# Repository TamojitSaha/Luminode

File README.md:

<h1 align="center"> LumiNode </h1> <br>

## Table of Contents
- [Introduction](#introduction)
- [Bill of Materials](#bill-of-materials)
- [Features](#features)
- [Contributors](#Contributors)
- [License](#license)
- [Acknowledgments](#acknowledgments)

## Introduction

A wireless multipurpose IoT (Internet of Things) compatible smart light system that can reproduce colour from any image in RGB colour space with intensity adjustment capability.
It is open-source and built for Arduino ecosystem making it suitable for hobbysist and beginners.
<p align="center">
  &nbsp 
  &nbsp 
</p>
<p align="center">
  &nbsp
  &nbsp
</p>
<p align="center">
  &nbsp
</p>

## Bill of Materials

        1. Arduino Pro Mini
        2. 7805 Voltage regulator
        3. Bluetooth module HC-05
        4. 4 x 3528 RGB LEDs
        5. 4 x 100 to 330ohm resistors in 0805 package
        6. 1 x ULN2003 smd
        7. 1 x MMBT2N2222
        8. 1 x 1Kohm in 0805 package
        9. 4 x 330ohm in 1206 package
        10. 1 x M7 diode(1N4007 smd version) 
        11. 1W cool white smd LED
        12. PCB fabrication materials.
        13. Single core wires for soldering PTH holes.
        14. DBS107G - Bridge Rectifier
        15. 2 x 10K in 1206 package
        16. 2 x 100nF in 0805 package
        17. 1 x ferrite chip 0805 package(optional: pads can be shorted in PCB)
        18. 1 x 1A PTC 0805 package(optional: pads can be shorted in PCB

## Features
- Simple UI
- Colour selection from any chosen image
- Real-time colour synchronization

## Contributors
Connect us here:
<br><br>
 <br>
 
<p> 
or <a href ="https://github.com/SandeepanSengupta/Luminode/issues/new/">file an issue</a>. Feature requests are always welcome.</p>

## License
Contents of this repository are realeased under [CC-BY-NC-SA 4.0](./LICENSE.md) <br>

## Acknowledgments
Thanks to the contributors! :wink:

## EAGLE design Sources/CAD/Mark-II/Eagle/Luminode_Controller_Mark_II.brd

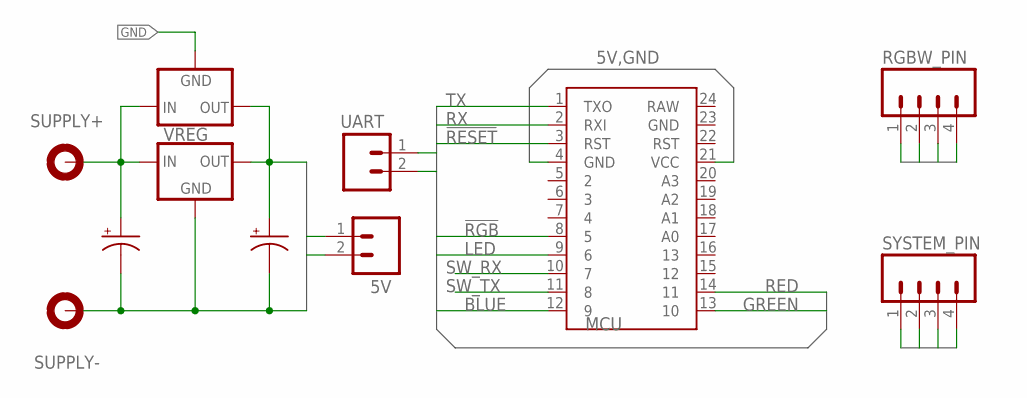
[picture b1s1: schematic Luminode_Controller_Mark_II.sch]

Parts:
5V: M02PTH; 1X02
C_IN: CPOL-USSMCB; SMC_B
C_OUT: CPOL-USSMCB; SMC_B
MCU: ARDUINO_MINI
RGBW_PIN: M04PTH; 1X04
SUPPLY+: +V; 3,0-PAD
SUPPLY-: -V; 3,0-PAD
SYSTEM_PIN: M04PTH; 1X04
UART: M02PTH; 1X02
VREG: 7805; SOT223
VREG_ALT: V_REG_78XXSINK; TO220-IGO

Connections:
5V: 5V.1, C_OUT.+, MCU.21 (VCC), SYSTEM_PIN.1, VREG.2 (OUT), VREG_ALT.OUT
!RESET: MCU.3 (RST)
!RGB: MCU.8 (5), SYSTEM_PIN.4
BLUE: MCU.12 (9), RGBW_PIN.3
GND: 5V.2, C_IN.-, C_OUT.-, MCU.4 (GND), SUPPLY-.B3,0, SYSTEM_PIN.3, VREG.1 (GND), VREG_ALT.GND
GREEN: MCU.13 (10), RGBW_PIN.2
LED: MCU.9 (6), RGBW_PIN.4
RED: MCU.14 (11), RGBW_PIN.1
RX: MCU.2 (RXI)
SW_RX: MCU.10 (7), UART.2
SW_TX: MCU.11 (8), UART.1
TX: MCU.1 (TXO)
VIN: C_IN.+, SUPPLY+.B3,0, SYSTEM_PIN.2, VREG.3 (IN), VREG_ALT.IN

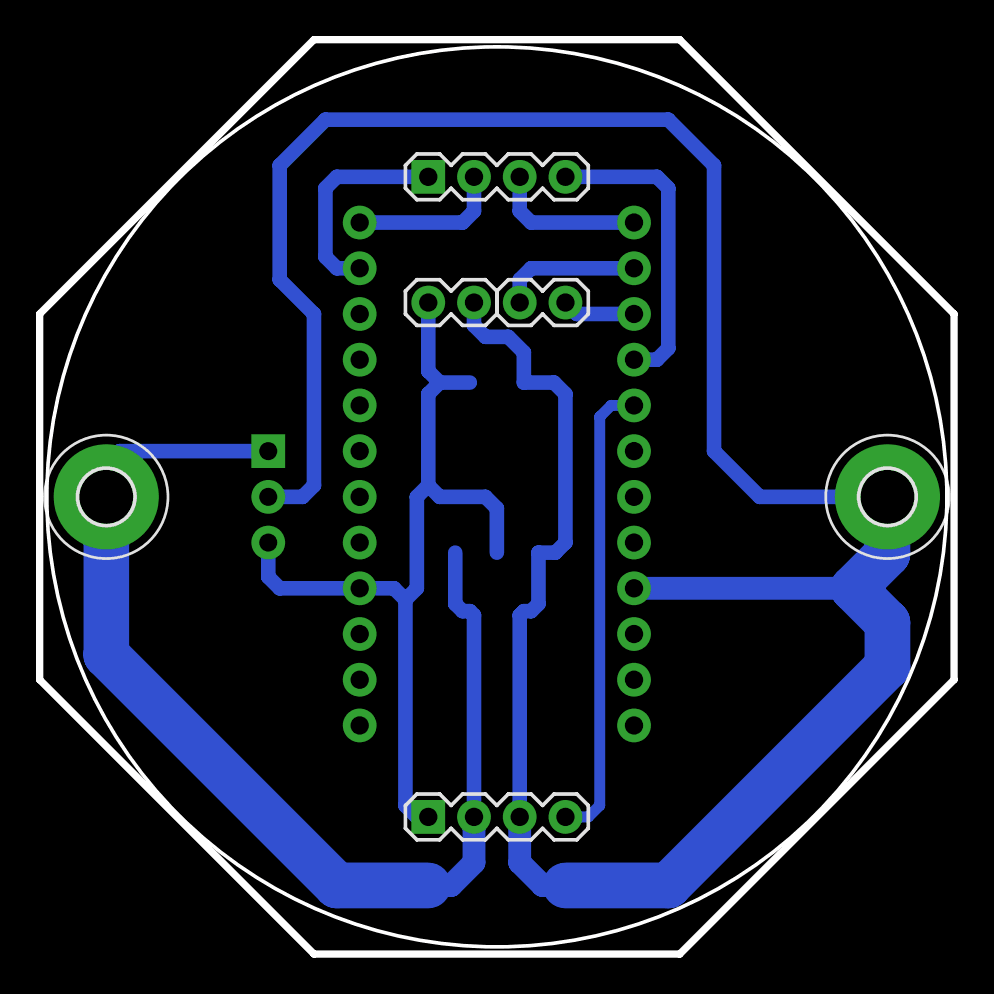
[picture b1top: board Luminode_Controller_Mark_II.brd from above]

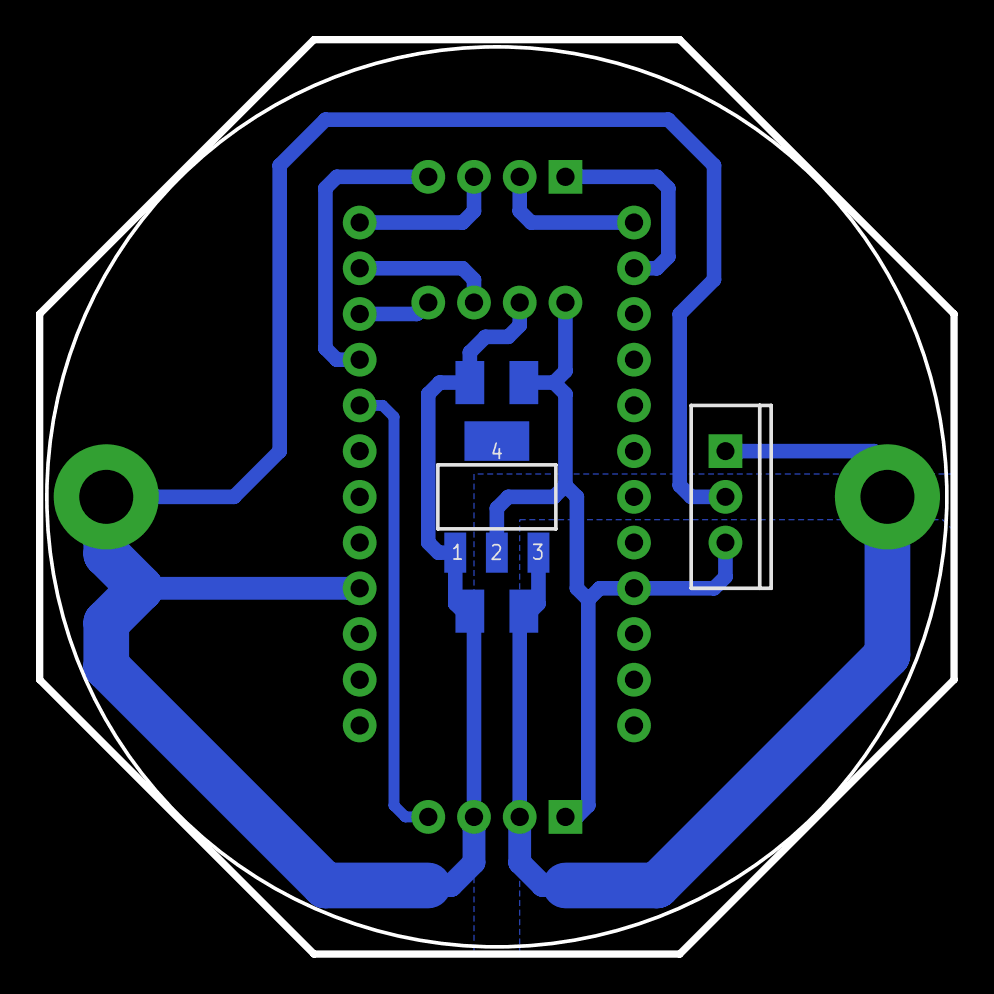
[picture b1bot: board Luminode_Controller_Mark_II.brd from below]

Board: 2 copper layers, 50.8 x 50.8 mm, 11 parts (4 on the bottom side), 10 nets.

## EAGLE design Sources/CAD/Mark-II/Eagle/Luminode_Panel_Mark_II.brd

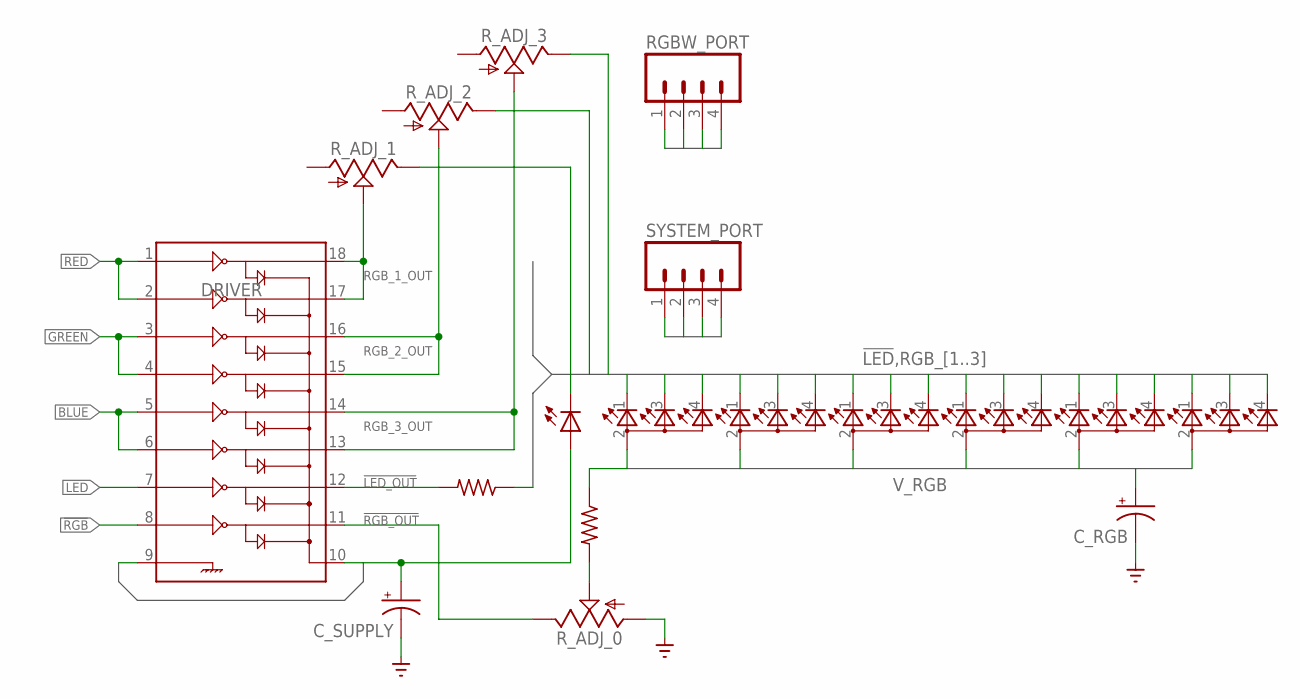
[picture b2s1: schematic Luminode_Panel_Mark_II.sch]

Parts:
C_RGB: CPOL-USE2.5-6; E2,5-6
C_SUPPLY: CPOL-USE2.5-6; E2,5-6
DRIVER: ULN2803SOICW; SO18L
LED: X42180; Z-POWER-LED-DOME-TYPE
LED_RGB_1, LED_RGB_2, LED_RGB_3, LED_RGB_4, LED_RGB_5, LED_RGB_6: TOPLED-3PLCC; P-LCC-4-3
RGBW_PORT: M04PTH; 1X04
R_ADJ_0, R_ADJ_1, R_ADJ_2, R_ADJ_3: 500E; B25P
R_LED: R-US_0309/10; 0309/10
R_RGB: R-US_0207/7; 0207/7
SYSTEM_PORT: M04PTH; 1X04

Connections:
5V: SYSTEM_PORT.1
!LED: LED.C, R_LED.1
!LED_OUT: DRIVER.12, R_LED.2
!RGB: DRIVER.8, SYSTEM_PORT.4
!RGB_OUT: DRIVER.11, R_ADJ_0.E
BLUE: DRIVER.5, DRIVER.6, RGBW_PORT.3
GND: C_RGB.-, C_SUPPLY.-, DRIVER.9, R_ADJ_0.A, SYSTEM_PORT.3
GREEN: DRIVER.3, DRIVER.4, RGBW_PORT.2
LED: DRIVER.7, RGBW_PORT.4
unnamed: R_ADJ_0.S, R_RGB.2
RED: DRIVER.1, DRIVER.2, RGBW_PORT.1
RGB_1: LED_RGB_1.1 (CRED), LED_RGB_2.1 (CRED), LED_RGB_3.1 (CRED), LED_RGB_4.1 (CRED), LED_RGB_5.1 (CRED), LED_RGB_6.1 (CRED), R_ADJ_1.E
RGB_1_OUT: DRIVER.17, DRIVER.18, R_ADJ_1.S
RGB_2: LED_RGB_1.3 (CBLUE), LED_RGB_2.3 (CBLUE), LED_RGB_3.3 (CBLUE), LED_RGB_4.3 (CBLUE), LED_RGB_5.3 (CBLUE), LED_RGB_6.3 (CBLUE), R_ADJ_2.E
RGB_2_OUT: DRIVER.15, DRIVER.16, R_ADJ_2.S
RGB_3: LED_RGB_1.4 (CGREEN), LED_RGB_2.4 (CGREEN), LED_RGB_3.4 (CGREEN), LED_RGB_4.4 (CGREEN), LED_RGB_5.4 (CGREEN), LED_RGB_6.4 (CGREEN), R_ADJ_3.E
RGB_3_OUT: DRIVER.13, DRIVER.14, R_ADJ_3.S
VIN: C_SUPPLY.+, DRIVER.10, LED.A, SYSTEM_PORT.2
V_RGB: C_RGB.+, LED_RGB_1.2 (A2), LED_RGB_2.2 (A2), LED_RGB_3.2 (A2), LED_RGB_4.2 (A2), LED_RGB_5.2 (A2), LED_RGB_6.2 (A2), R_RGB.1

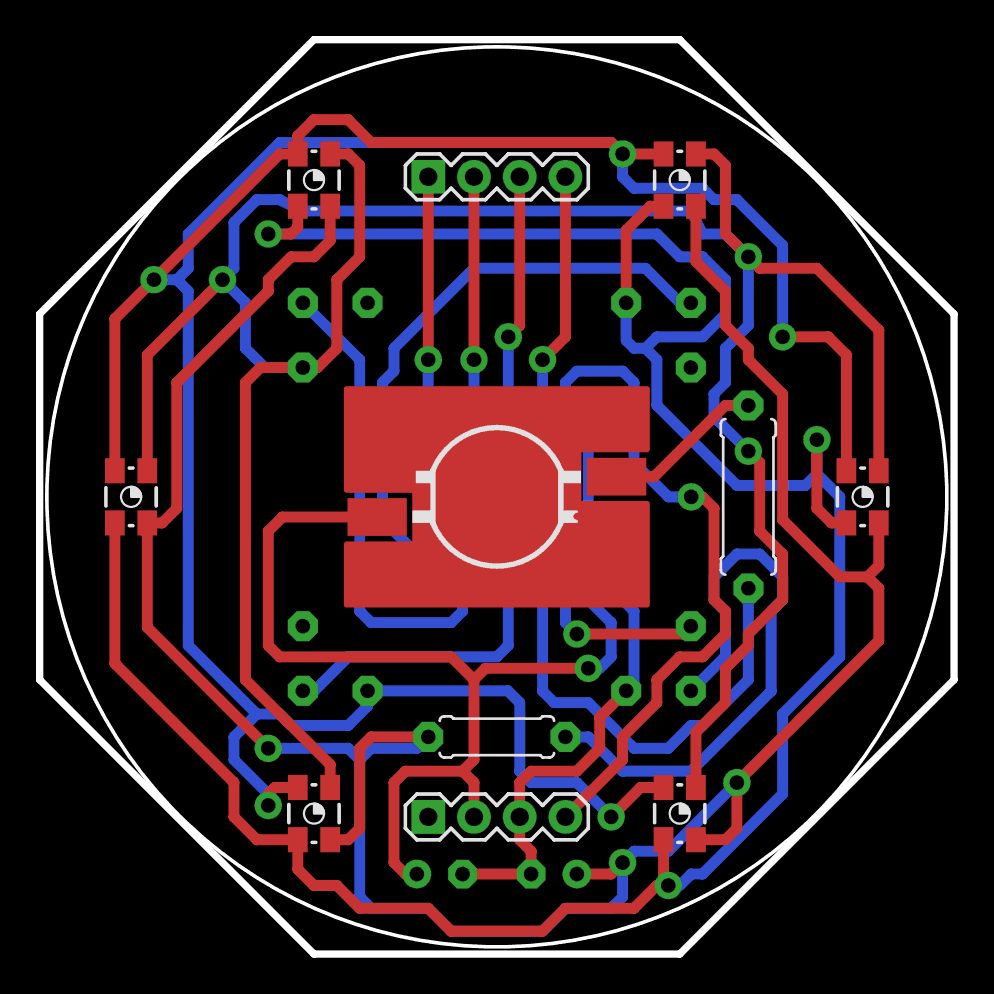
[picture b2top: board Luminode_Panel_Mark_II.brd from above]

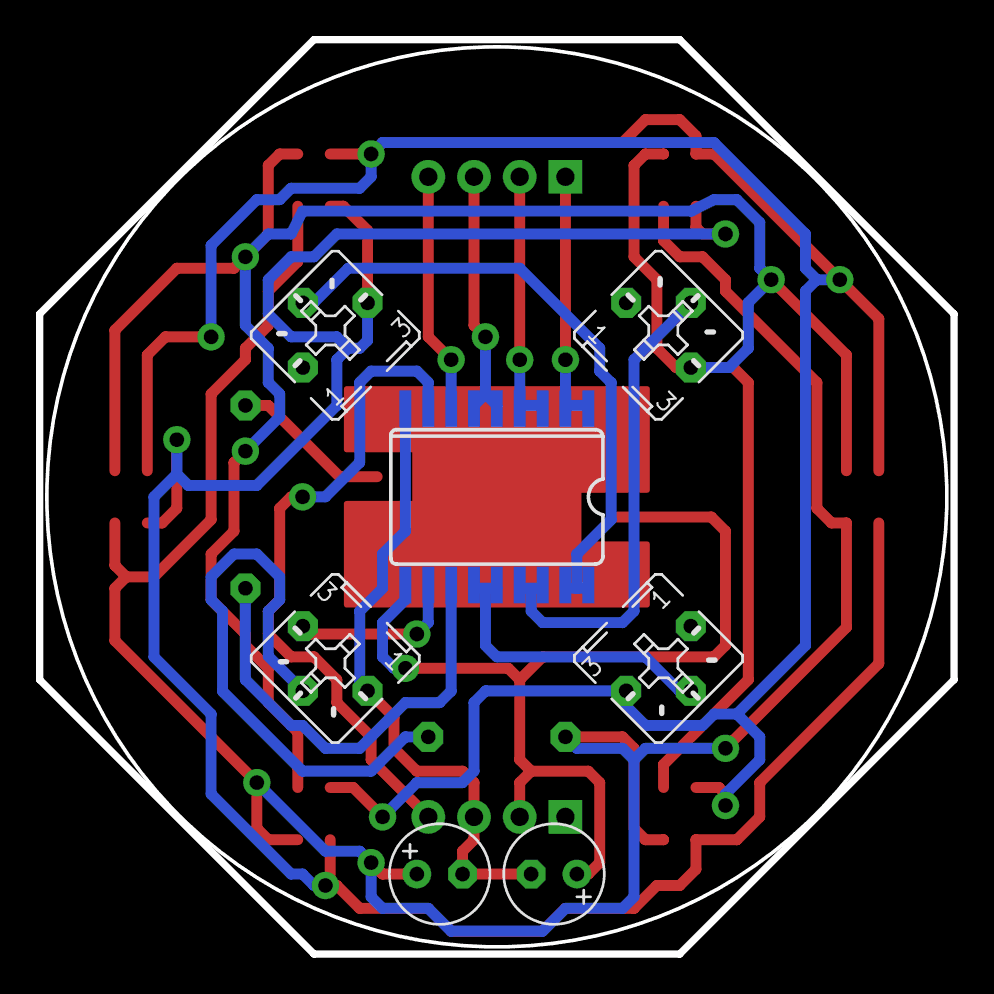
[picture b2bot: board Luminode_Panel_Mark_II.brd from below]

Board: 2 copper layers, 50.8 x 50.8 mm, 18 parts (7 on the bottom side), 18 nets.

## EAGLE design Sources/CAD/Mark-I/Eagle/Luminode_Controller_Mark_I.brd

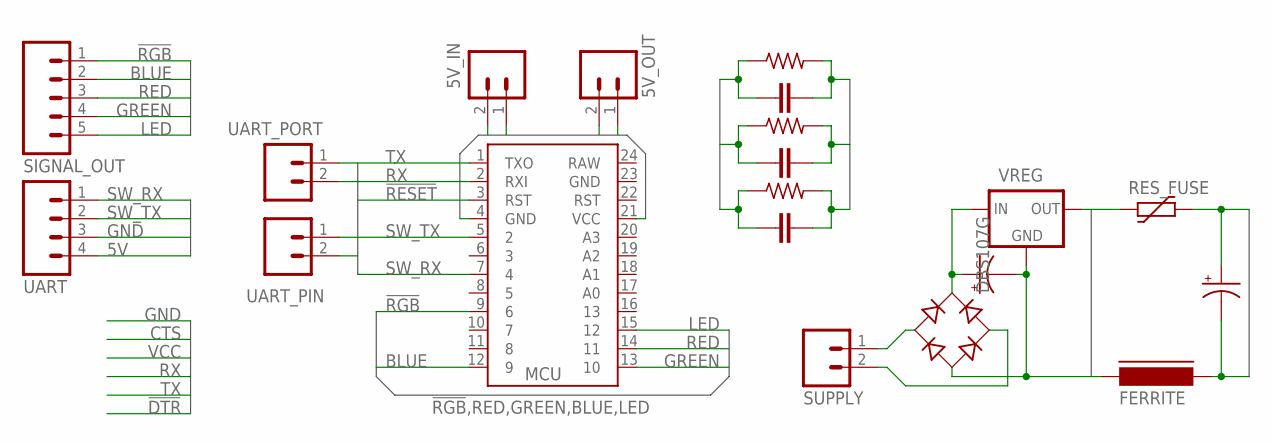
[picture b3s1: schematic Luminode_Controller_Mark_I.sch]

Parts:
5V_IN, 5V_OUT: M02PTH; 1X02
C_BLUE: C-EUC0805K; C0805K
C_GREEN: C-EUC0805K; C0805K
C_IN: CPOL-USSMCB; SMC_B
C_OUT: CPOL-USSMCB; SMC_B
C_RED: C-EUC0805K; C0805K
FERRITE: FERRITE-0805; FB805
MCU: ARDUINO_MINI
RECTIFIER: DBS107G; DBS
RES_FUSE: FUSE_PTC-0805; PTC0805
R_BLUE: R-US_M1206; M1206
R_GREEN: R-US_M1206; M1206
R_RED: R-US_M1206; M1206
SIGNAL_OUT: M05PTH; 1X05
SUPPLY: M02PTH; 1X02
UART: M04PTH; 1X04
UART_PIN: M02PTH; 1X02
UART_PORT: M02PTH; 1X02
VREG: 7805; SOT223

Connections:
5V: 5V_IN.1, 5V_OUT.1, C_OUT.+, MCU.21 (VCC), RES_FUSE.2, UART.4
!RESET: MCU.3 (RST)
!RGB: MCU.9 (6), SIGNAL_OUT.1
AC_EARTH: RECTIFIER.AC2, SUPPLY.2
AC_IN: RECTIFIER.AC1, SUPPLY.1
BLUE: C_BLUE.2, MCU.12 (9), R_BLUE.1, SIGNAL_OUT.2
EARTH: C_IN.-, FERRITE.2, RECTIFIER.-, VREG.1 (GND)
GND: 5V_IN.2, 5V_OUT.2, C_BLUE.1, C_GREEN.1, C_OUT.-, C_RED.1, FERRITE.1, MCU.4 (GND), R_BLUE.2, R_GREEN.2, R_RED.2, UART.3
GREEN: C_GREEN.2, MCU.13 (10), R_GREEN.1, SIGNAL_OUT.4
LED: MCU.15 (12), SIGNAL_OUT.5
RED: C_RED.2, MCU.14 (11), R_RED.1, SIGNAL_OUT.3
RX: MCU.2 (RXI)
SW_RX: MCU.7 (4), UART.1, UART_PIN.2, UART_PORT.2
SW_TX: MCU.5 (2), UART.2, UART_PIN.1, UART_PORT.1
TX: MCU.1 (TXO)
VIN: C_IN.+, RECTIFIER.+, VREG.3 (IN)
VOUT: RES_FUSE.1, VREG.2 (OUT)

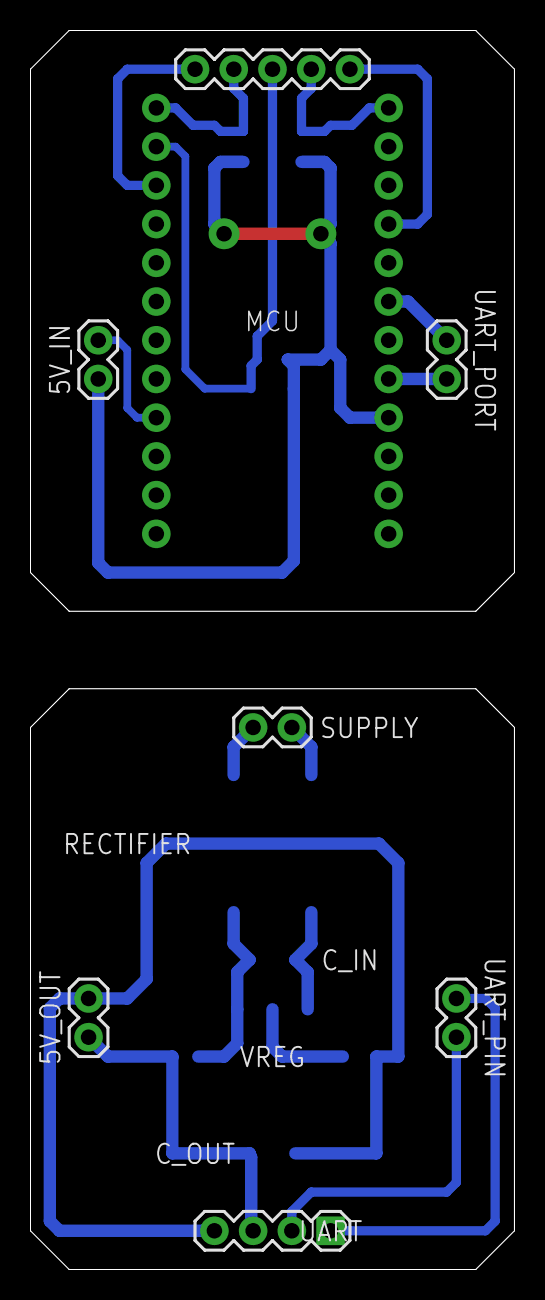
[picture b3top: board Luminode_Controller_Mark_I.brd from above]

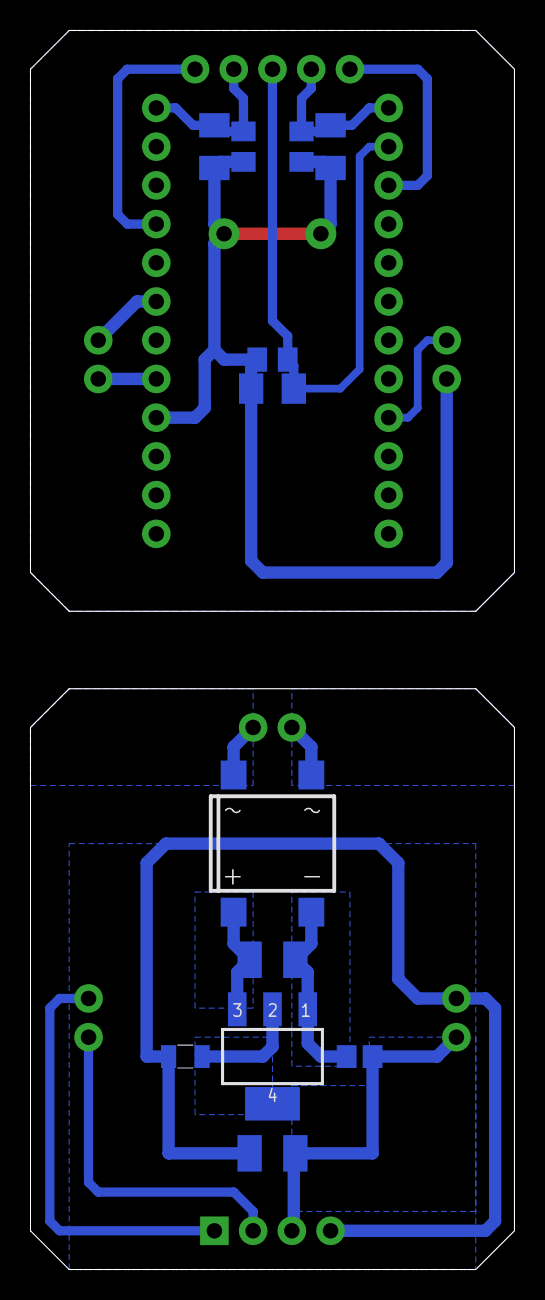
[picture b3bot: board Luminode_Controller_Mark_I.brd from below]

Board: 2 copper layers, 31.8 x 81.3 mm, 20 parts (12 on the bottom side), 14 nets.

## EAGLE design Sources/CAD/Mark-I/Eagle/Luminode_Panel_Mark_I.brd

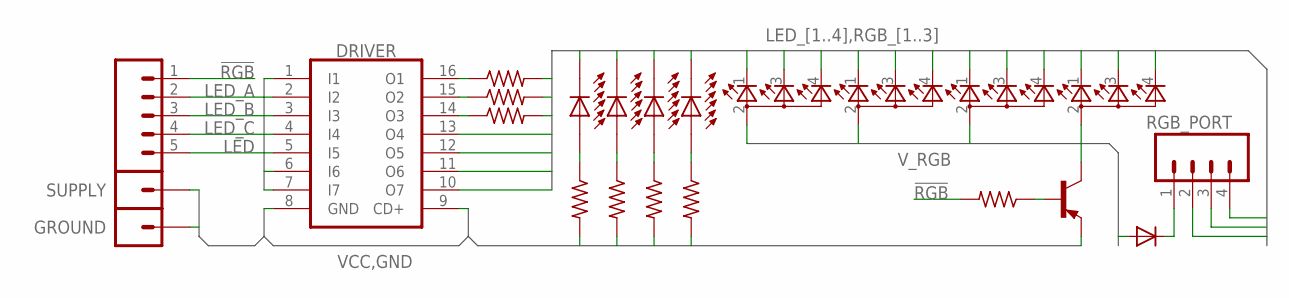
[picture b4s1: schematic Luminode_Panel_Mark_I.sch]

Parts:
DIODE: DIODE-DO-214AC; DO-214AC
DRIVER: ULN2003AD; SO16
GROUND: M01PTH; 1X01
LED_1, LED_2, LED_3, LED_4: LXHL-DB01; SIDE-EMITTING
LED_RGB_1, LED_RGB_2, LED_RGB_3, LED_RGB_4: TOPLED-3PLCC; P-LCC-4-3
RGB_PORT: M04SMD; 1X04-SMD
R_LED_1, R_LED_2, R_LED_3, R_LED_4: 100E; M1206
R_RGB: 100E; M0805
R_RGB_A: 100E; M0805
R_RGB_B: 100E; M0805
R_RGB_C: 100E; M0805
SIGNAL: M05PTH; 1X05
SUPPLY: M01PTH; 1X01
TRANSISTOR: BC807-16-PNP-SOT23-BEC; SOT23-BEC

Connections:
!RGB: R_RGB.2, SIGNAL.1
GND: DRIVER.8 (GND), GROUND.1
LED: DRIVER.4 (I4), DRIVER.5 (I5), DRIVER.6 (I6), DRIVER.7 (I7), SIGNAL.5
LED_1: DRIVER.13 (O4), LED_1.CATHODE (C)
LED_2: DRIVER.10 (O7), LED_2.CATHODE (C)
LED_3: DRIVER.11 (O6), LED_3.CATHODE (C)
LED_4: DRIVER.12 (O5), LED_4.CATHODE (C)
LED_A: DRIVER.1 (I1), SIGNAL.2
LED_B: DRIVER.2 (I2), SIGNAL.3
LED_C: DRIVER.3 (I3), SIGNAL.4
unnamed: DRIVER.16 (O1), R_RGB_A.1
unnamed: DRIVER.15 (O2), R_RGB_B.1
unnamed: DRIVER.14 (O3), R_RGB_C.1
unnamed: LED_1.ANODE (A), R_LED_1.1
unnamed: LED_2.ANODE (A), R_LED_2.1
unnamed: LED_3.ANODE (A), R_LED_3.1
unnamed: LED_4.ANODE (A), R_LED_4.1
unnamed: R_RGB.1, TRANSISTOR.B
RGB_1: LED_RGB_1.1 (CRED), LED_RGB_2.1 (CRED), LED_RGB_3.1 (CRED), LED_RGB_4.1 (CRED), RGB_PORT.4, R_RGB_A.2
RGB_2: LED_RGB_1.3 (CBLUE), LED_RGB_2.3 (CBLUE), LED_RGB_3.3 (CBLUE), LED_RGB_4.3 (CBLUE), RGB_PORT.3, R_RGB_B.2
RGB_3: LED_RGB_1.4 (CGREEN), LED_RGB_2.4 (CGREEN), LED_RGB_3.4 (CGREEN), LED_RGB_4.4 (CGREEN), RGB_PORT.2, R_RGB_C.2
RGB_EXT: DIODE.C, RGB_PORT.1
VCC: DRIVER.9 (CD+), R_LED_1.2, R_LED_2.2, R_LED_3.2, R_LED_4.2, SUPPLY.1, TRANSISTOR.E
V_RGB: DIODE.A, LED_RGB_1.2 (A2), LED_RGB_2.2 (A2), LED_RGB_3.2 (A2), LED_RGB_4.2 (A2), TRANSISTOR.C

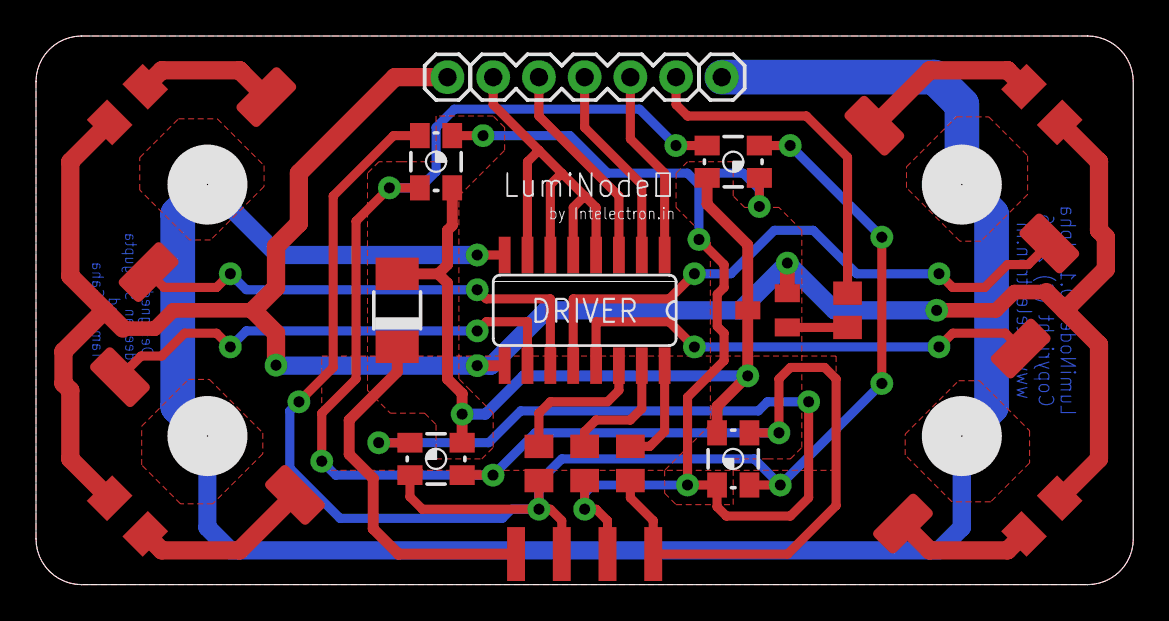
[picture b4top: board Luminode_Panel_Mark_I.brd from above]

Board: 2 copper layers, 61.0 x 30.5 mm, 23 parts (0 on the bottom side), 24 nets.

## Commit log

2017-12-04 Create about
2017-12-05 Android App
2017-12-05 Video

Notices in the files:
Sources/CAD/Mark-I/Eagle/Luminode_Panel_Mark_I.brd:
Copyright (C) 2016
parts and their libraries:
SparkFun-Boards: Licensing: Creative Commons ShareAlike 4.0 International - https://creativecommons.org/licenses/by-sa/4.0
SparkFun-Connectors: Licensing: CC v3.0 Share-Alike You are welcome to use this library for commercial purposes.
